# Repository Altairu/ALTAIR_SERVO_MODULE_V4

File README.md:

# [ALTAIR_SERVO_MODULE_V4](https://github.com/Altairu/ALTAIR_SERVO_MODULE_V4)
ALTAIR_SERVO_MODULE_V4

### サーボモータ×８ ピン番号
  * B6 tim2_ch1
  * B7 tim4_ch2
  * B8 tim2_ch1 tim4_ch3 timer10_ch1 
  * B9 tim2_ch2 tim4_ch4 tim11_ch1
  * C6 tim3_ch1 tim8_ch1
  * C7 tim3_ch2 tim8_ch2
  * C8 tim3_ch3 tim8_ch3
  * C9 tim3_ch4 tim8_ch4

### フォトカプラ
[TLP291](https://akizukidenshi.com/catalog/g/g116298/)

### 回路図

### PCB

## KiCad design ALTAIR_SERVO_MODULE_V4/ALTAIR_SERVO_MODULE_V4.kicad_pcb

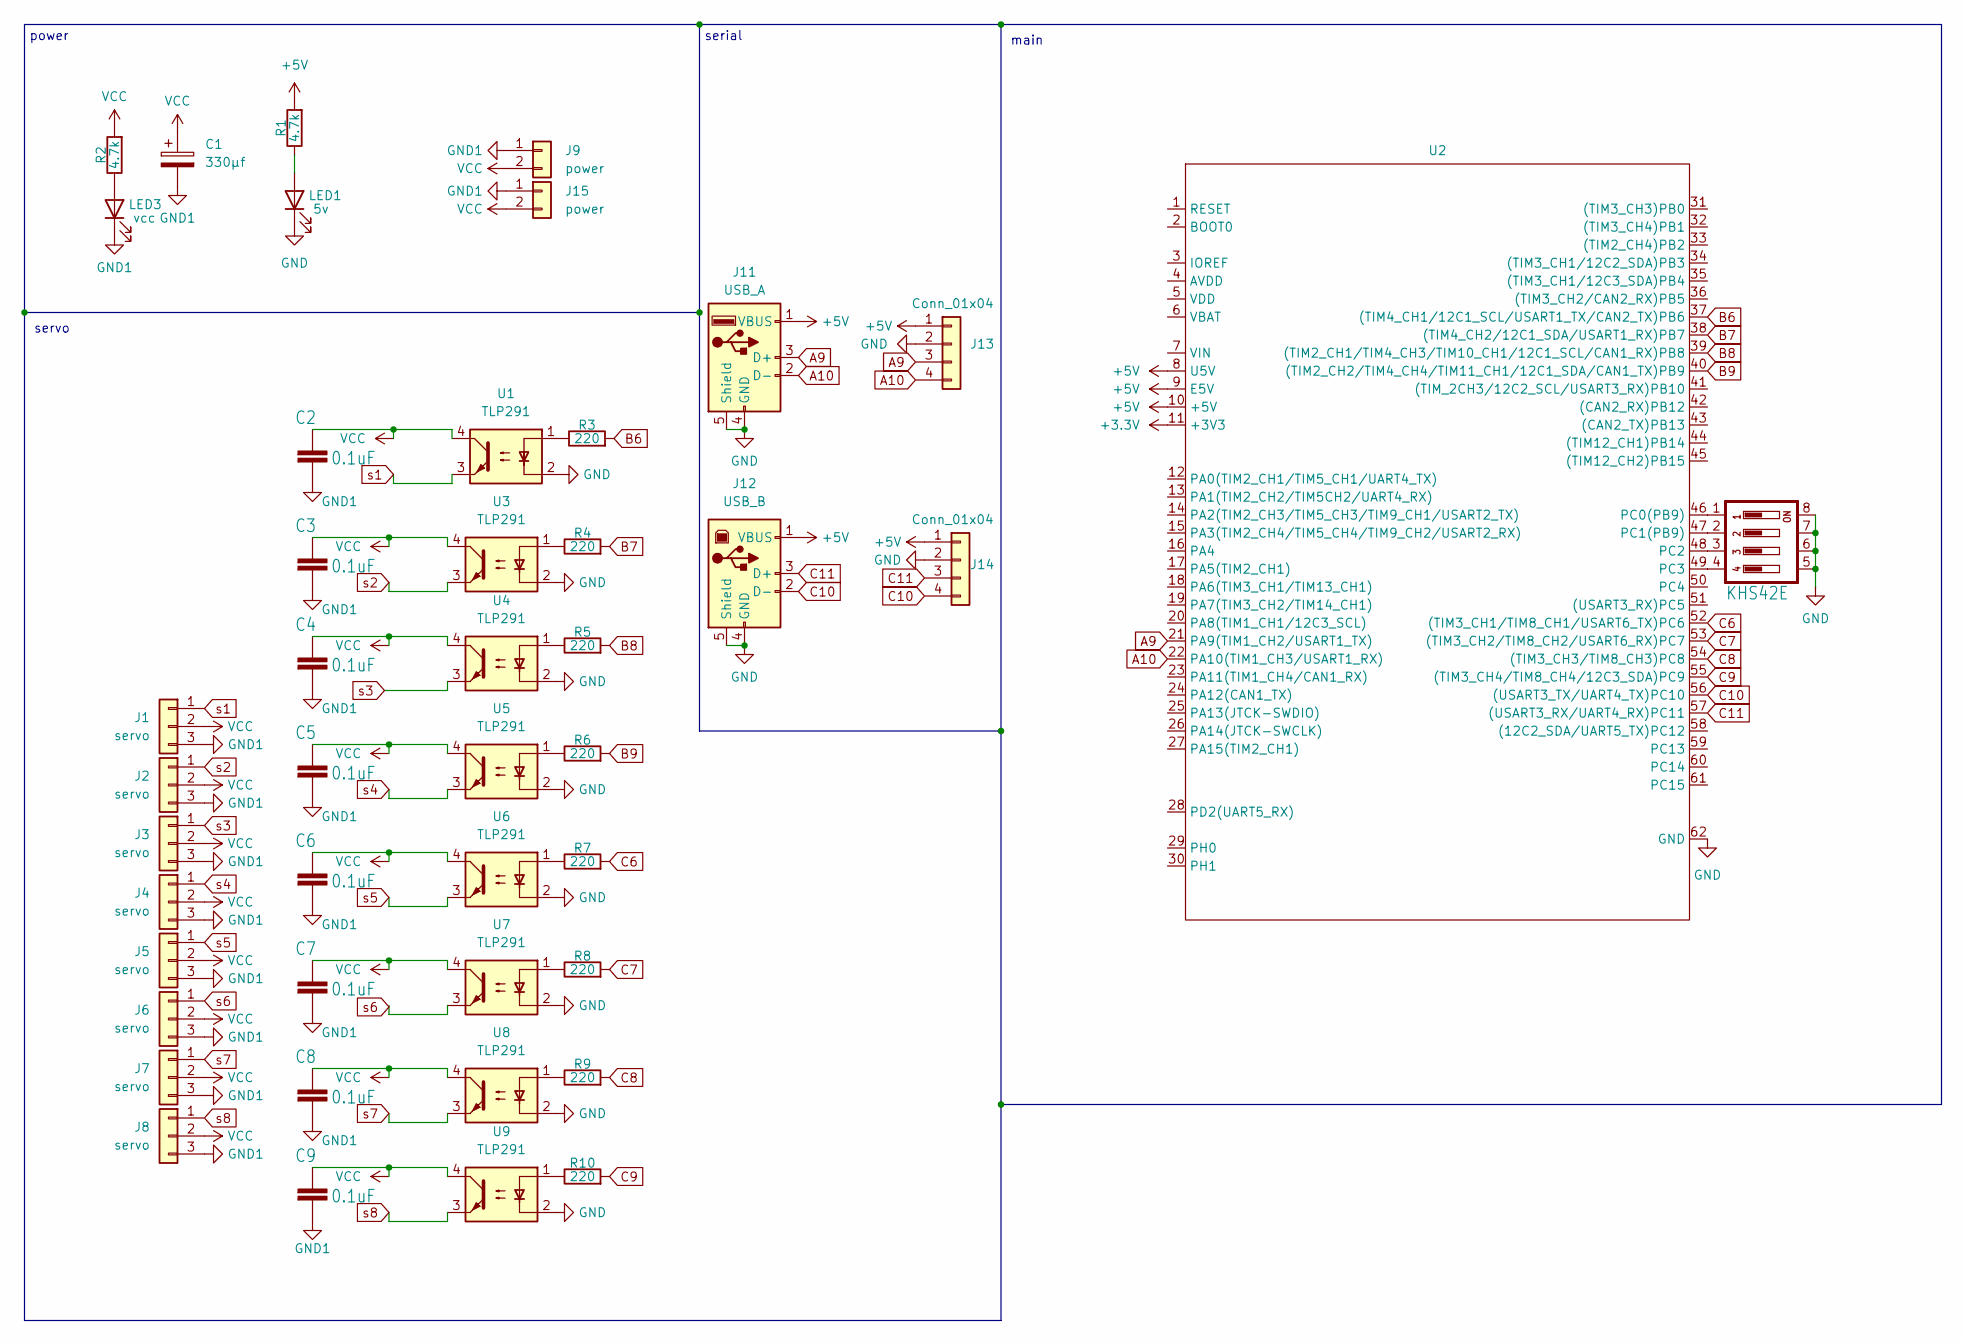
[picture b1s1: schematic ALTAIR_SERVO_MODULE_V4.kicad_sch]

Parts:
C1: 330μf; CP_Elec_10x10
C2, C3, C4, C5, C6, C7, C8, C9: 0.1uF; C_0603_1608Metric
J1, J2, J3, J4, J5, J6, J7, J8: servo; JST_XA_S03B-XASK-1_1x03_P2.50mm_Horizontal
J9, J15: power; AMASS_XT60PW-M_1x02_P7.20mm_Horizontal
J11: USB_A; USB_A_Molex_67643_Horizontal
J12: USB_B; USB_B_Lumberg_2411_02_Horizontal
J13, J14: Conn_01x04; JST_XA_B04B-XASK-1_1x04_P2.50mm_Vertical
LED1: 5v; LED_0603_1608Metric
LED3: vcc; LED_0603_1608Metric
R1, R2: 4.7k; R_0603_1608Metric
R3, R4, R5, R6, R7, R8, R9, R10: 220; R_0603_1608Metric
S2: KHS42E; SOIC127P600X175-8N
U1, U3, U4, U5, U6, U7, U8, U9: TLP291; SOIC-4_4.55x2.6mm_P1.27mm
U2: STM32F446RE_Nucleo

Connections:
+3.3V: U2.11 (+3V3)
+5V: J11.1 (VBUS), J12.1 (VBUS), J13.1, J14.1, R1.2, U2.8 (U5V), U2.9 (E5V), U2.10 (+5V)
A9: J11.3 (D+), J13.3, U2.21 (PA9(TIM1_CH2/USART1_TX))
A10: J11.2 (D-), J13.4, U2.22 (PA10(TIM1_CH3/USART1_RX))
B6: R3.2, U2.37 ((TIM4_CH1/12C1_SCL/USART1_TX/CAN2_TX)PB6)
B7: R4.2, U2.38 ((TIM4_CH2/12C1_SDA/USART1_RX)PB7)
B8: R5.2, U2.39 ((TIM2_CH1/TIM4_CH3/TIM10_CH1/12C1_SCL/C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)
B9: R6.2, U2.40 ((TIM2_CH2/TIM4_CH4/TIM11_CH1/12C1_SDA/C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)
C6: R7.2, U2.52 ((TIM3_CH1/TIM8_CH1/USART6_TX)PC6)
C7: R8.2, U2.53 ((TIM3_CH2/TIM8_CH2/USART6_RX)PC7)
C8: R9.2, U2.54 ((TIM3_CH3/TIM8_CH3)PC8)
C9: R10.2, U2.55 ((TIM3_CH4/TIM8_CH4/12C3_SDA)PC9)
C10: J12.2 (D-), J14.4, U2.56 ((USART3_TX/UART4_TX)PC10)
C11: J12.3 (D+), J14.3, U2.57 ((USART3_RX/UART4_RX)PC11)
GND: J11.4 (GND), J11.5 (Shield), J12.4 (GND), J12.5 (Shield), J13.2, J14.2, LED1.1 (K), S2.5, S2.6, S2.7, S2.8, U1.2, U2.62 (GND), U3.2, U4.2, U5.2, U6.2, U7.2, U8.2, U9.2
GND1: C1.2, C2.2, C3.2, C4.2, C5.2, C6.2, C7.2, C8.2, C9.2, J1.3, J2.3, J3.3, J4.3, J5.3, J6.3, J7.3, J8.3, J9.1, J15.1, LED3.1 (K)
unnamed: LED1.2 (A), R1.1
unnamed: LED3.2 (A), R2.1
unnamed: R3.1, U1.1
unnamed: R4.1, U3.1
unnamed: R5.1, U4.1
unnamed: R6.1, U5.1
unnamed: R7.1, U6.1
unnamed: R8.1, U7.1
unnamed: R9.1, U8.1
unnamed: R10.1, U9.1
unnamed: S2.1, U2.46 (PC0(PB9))
unnamed: S2.2, U2.47 (PC1(PB9))
unnamed: S2.3, U2.48 (PC2)
unnamed: S2.4, U2.49 (PC3)
VCC: C1.1, C2.1, C3.1, C4.1, C5.1, C6.1, C7.1, C8.1, C9.1, J1.2, J2.2, J3.2, J4.2, J5.2, J6.2, J7.2, J8.2, J9.2, J15.2, R2.2, U1.4, U3.4, U4.4, U5.4, U6.4, U7.4, U8.4, U9.4
s1: J1.1, U1.3
s2: J2.1, U3.3
s3: J3.1, U4.3
s4: J4.1, U5.3
s5: J5.1, U6.3
s6: J6.1, U7.3
s7: J7.1, U8.3
s8: J8.1, U9.3

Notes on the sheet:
serial
main
power
servo

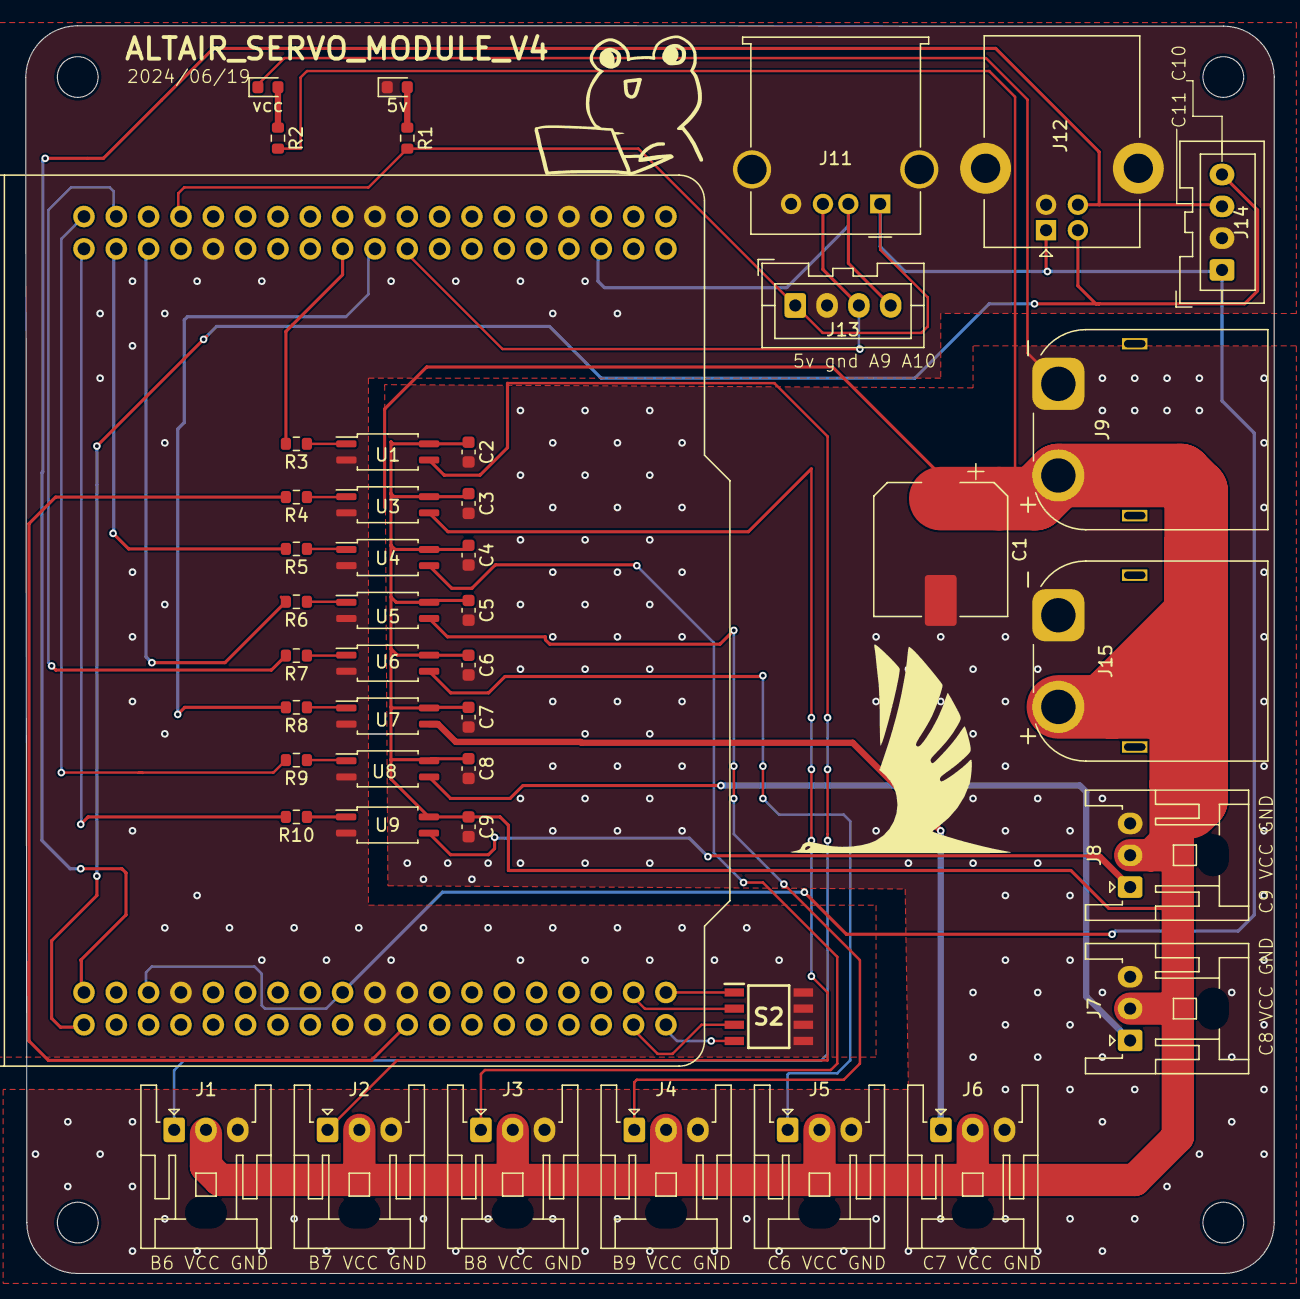
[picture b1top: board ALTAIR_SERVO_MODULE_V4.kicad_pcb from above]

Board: 2 copper layers, 98.1 x 98.0 mm, 45 parts (0 on the bottom side), 38 nets.
